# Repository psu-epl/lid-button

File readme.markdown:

LID Disco Button
----
Starting fresh? Go [here](https://github.com/psu-epl/lid-button/wiki)

Quick Links:

[Board Routing](https://github.com/psu-epl/lid-button/wiki/Board-Routing)

[Plating Thru Holes](https://github.com/psu-epl/lid-button/wiki/Plating-Thru-Holes)

[Testing the Board Part One](https://github.com/psu-epl/lid-button/wiki/Testing-the-board-Part-One)

[Solder Mask](https://github.com/psu-epl/lid-button/wiki/Applying-Solder-Mask)

[Solder Paste Stencil](https://github.com/psu-epl/lid-button/wiki/Solder-Paste-Stencil)

[Solder Paste](https://github.com/psu-epl/lid-button/wiki/Solder-Paste-Prep)

[Stuffing the board](https://github.com/psu-epl/lid-button/wiki/Stuffing-the-Board)

[Reflow Oven](https://github.com/psu-epl/lid-button/wiki/Reflow)

[Testing the Board Part Two](https://github.com/psu-epl/lid-button/wiki/Testing-The-Board-Part-Two)

[Programming the Microcontroller](https://github.com/psu-epl/lid-button/wiki/Coding-the-Board)

[Final Board Test](https://github.com/psu-epl/lid-button/wiki/Final-Board-Test)

[Enclosure Bottom](https://github.com/psu-epl/lid-button/wiki/Enclosure-Bottom)

[Enclosure Top](https://github.com/psu-epl/lid-button/wiki/Enclosure-Top)

[About this Project](https://github.com/psu-epl/lid-button/wiki/About-this-Project)

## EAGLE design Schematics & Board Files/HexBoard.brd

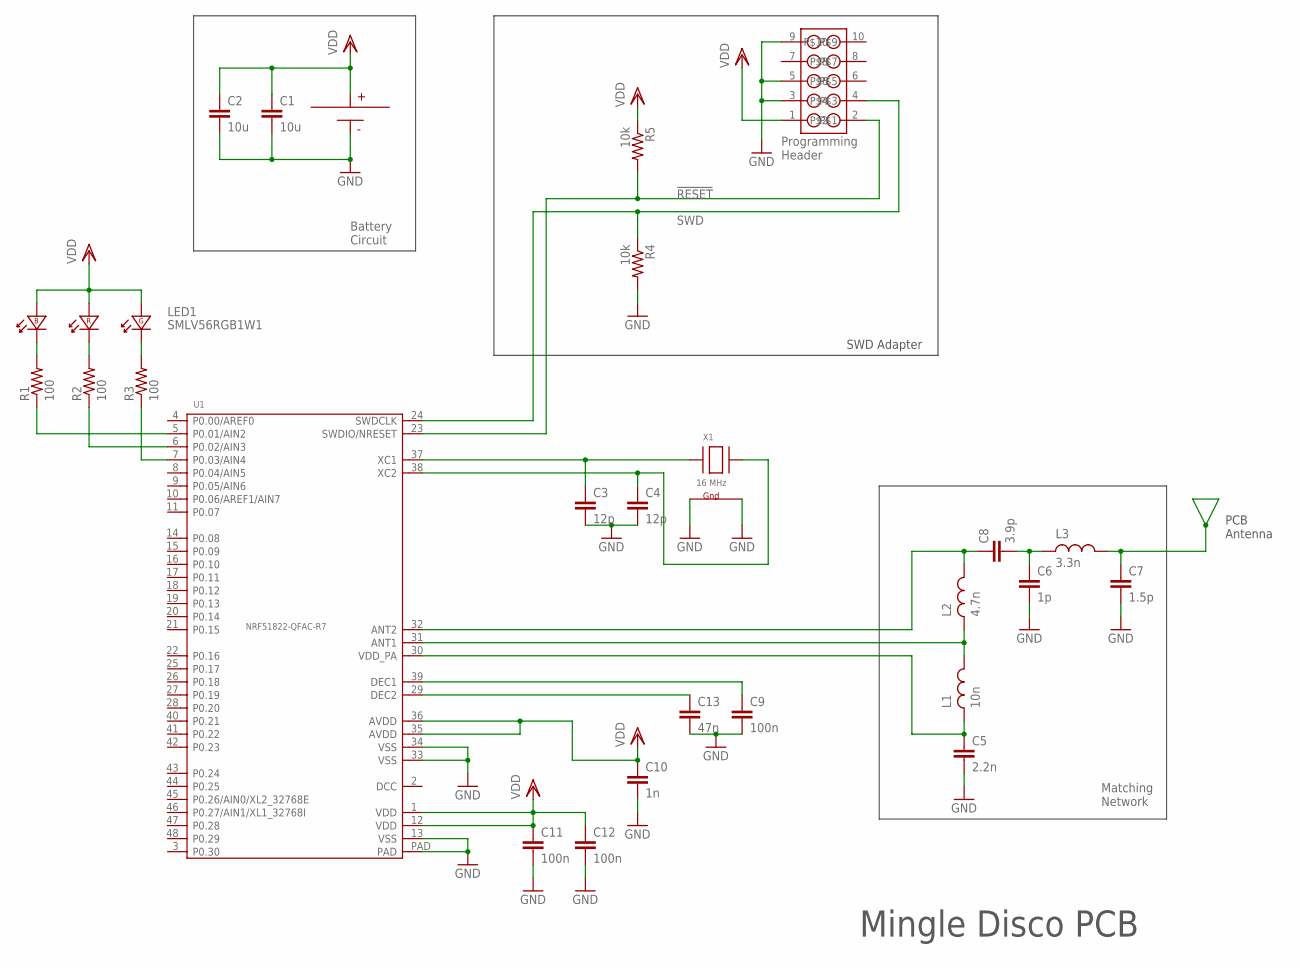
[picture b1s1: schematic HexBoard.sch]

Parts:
B1: CON-COINCEL-HOLDER-KEYSTONE-3012TR; 16MM-COINCELL-KEYSTONE
C1, C2: 10u; C0805
C3, C4: 12p; C0402
C5: 2.2n; C0402
C6: 1p; C0402
C7: 1.5p; C0402
C8: 3.9p; C0402
C9, C11, C12: 100n; C0402
C10: 1n; C0402
C13: 47n; C0402
L1: 10n; .0402-B-NOSILK
L2: 4.7n; .0402-B-NOSILK
L3: 3.3n; .0402-B-NOSILK
LED1: SMLV56RGB1W1; LED-3528
R1, R2, R3: 100; R0402
R4, R5: 10k; R0402
U1: NRF51822-QFAC-R7; QFN48-6X6MM
U$1: HEADER.05"PITCH
X1: 16 MHz; TXC_CRYSTAL

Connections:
!RESET: R5.2, U1.23 (SWDIO/NRESET), U$1.2
ANTENNA: C7.1, L3.2
GND: B1.NEG, C1.2, C2.2, C3.2, C4.2, C5.2, C6.2, C7.2, C9.2, C10.2, C11.2, C12.2, C13.2, R4.2, U1.13 (VSS), U1.33 (VSS), U1.34 (VSS), U1.PAD, U$1.3, U$1.5, U$1.9, X1.2 (G1), X1.4 (G2)
unnamed: LED1.6 (K), R1.2
unnamed: LED1.5 (K), R2.2
unnamed: LED1.4 (K), R3.2
unnamed: R1.1, U1.5 (P0.01/AIN2)
unnamed: R2.1, U1.6 (P0.02/AIN3)
unnamed: R3.1, U1.7 (P0.03/AIN4)
unnamed: C3.1, U1.37 (XC1), X1.1 (X1)
unnamed: C4.1, U1.38 (XC2), X1.3 (X2)
unnamed: L1.2, L2.1, U1.31 (ANT1)
unnamed: C9.1, U1.39 (DEC1)
unnamed: C6.1, C8.2, L3.1
unnamed: C8.1, L2.2, U1.32 (ANT2)
unnamed: C5.1, L1.1, U1.30 (VDD_PA)
unnamed: C13.1, U1.29 (DEC2)
SWD: R4.1, U1.24 (SWDCLK), U$1.4
VDD: B1.POS@1 (POS), B1.POS@2 (POS), C1.1, C2.1, C10.1, C11.1, C12.1, LED1.1 (A), LED1.2 (A), LED1.3 (A), R5.1, U1.1 (VDD), U1.12 (VDD), U1.35 (AVDD), U1.36 (AVDD), U$1.1

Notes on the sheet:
PCB Antenna
Battery Circuit
Programming Header
Matching Network
SWD Adapter
Mingle Disco PCB

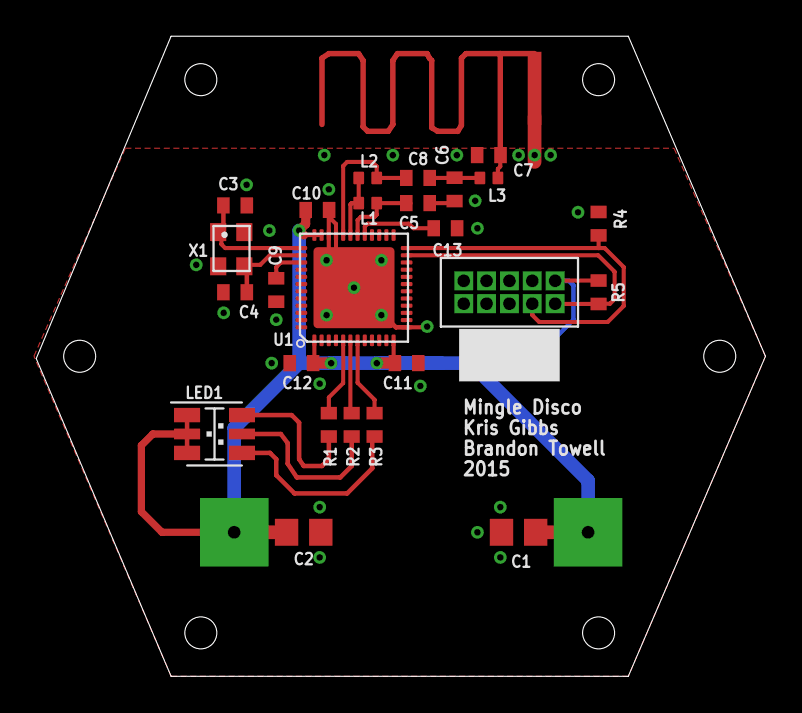
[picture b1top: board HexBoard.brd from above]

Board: 2 copper layers, 40.5 x 35.6 mm, 26 parts (1 on the bottom side), 19 nets.

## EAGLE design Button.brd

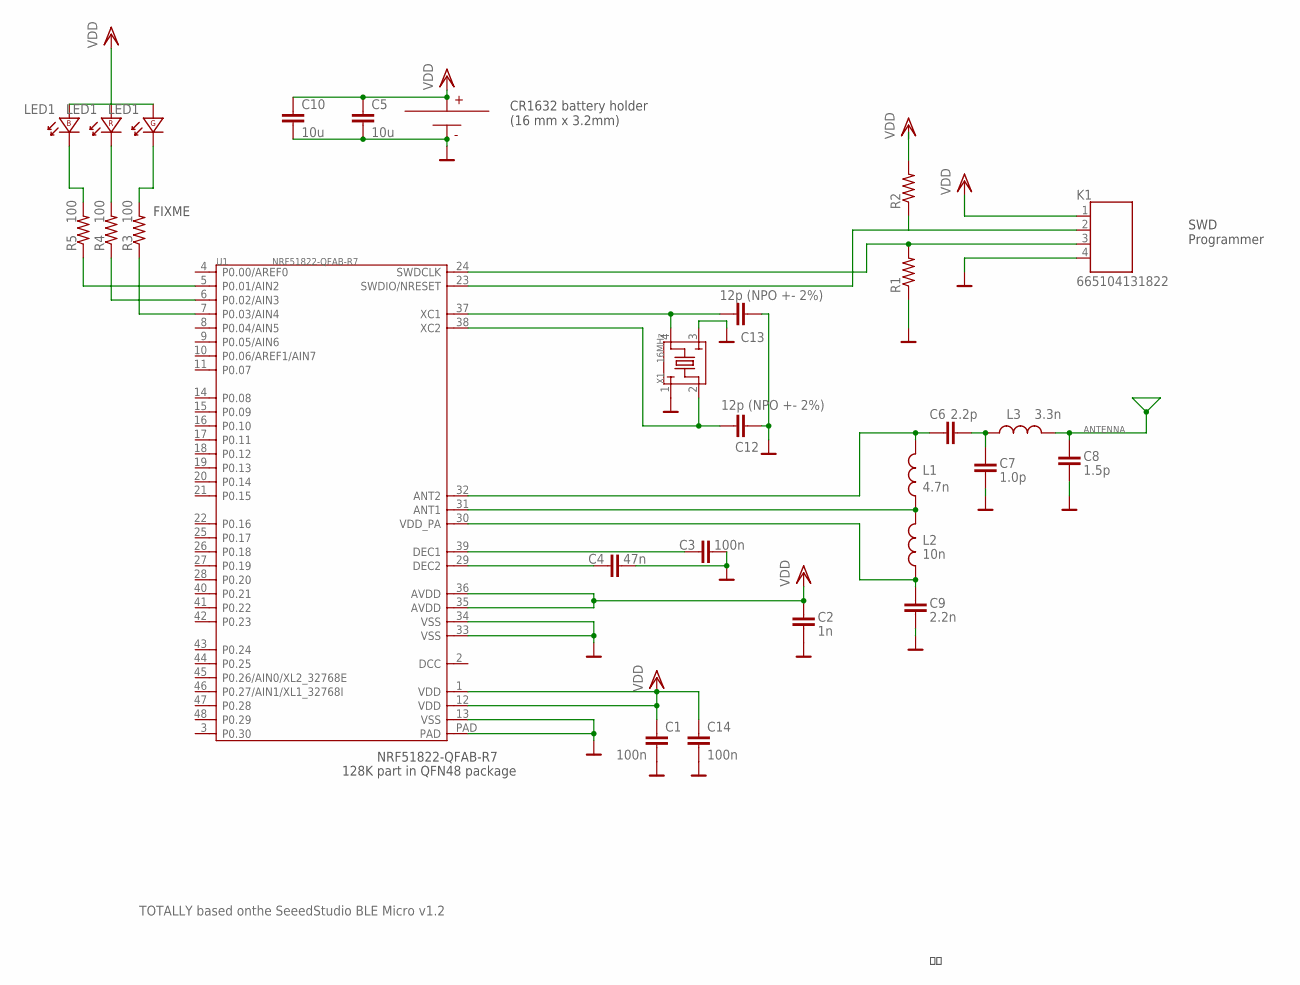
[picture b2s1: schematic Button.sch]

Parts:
B1: CON-COINCEL-HOLDER-KEYSTONE-3012TR; 16MM-COINCELL-KEYSTONE
C1, C3, C14: 100n; .0402-C-NOSILK
C2: 1n; .0402-C-NOSILK
C4: 47n; .0402-C-NOSILK
C5, C10: 10u; .0805-B-NOSILK
C6: 2.2p; .0402-C-NOSILK
C7: 1.0p; .0402-C-NOSILK
C8: 1.5p; .0402-C-NOSILK
C9: 2.2n; .0402-C-NOSILK
C12, C13: 12p (NPO +- 2%); .0402-C-NOSILK
K1: 665104131822
L1: 4.7n; .0402-C-NOSILK
L2: 10n; .0402-C-NOSILK
L3: 3.3n; .0402-C-NOSILK
LED1: LED-RGB-SEPARATE-3528; LED-3528
R1, R2: R-US_R0402; R0402
R3, R4, R5: 100; .0402-C-NOSILK
U1: NRF51822-QFAB-R7; QFN48-6X6MM
X1: 16MHz; 2520

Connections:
ANTENNA: C8.2, L3.2
GND: B1.NEG, C1.2, C2.2, C3.2, C4.2, C5.2, C7.1, C8.1, C9.2, C10.2, C12.2, C13.2, C14.2, K1.4, R1.1, U1.13 (VSS), U1.33 (VSS), U1.34 (VSS), U1.PAD, X1.1, X1.3
unnamed: R5.1, U1.5 (P0.01/AIN2)
unnamed: R4.1, U1.6 (P0.02/AIN3)
unnamed: R3.1, U1.7 (P0.03/AIN4)
unnamed: LED1.6 (K), R5.2
unnamed: LED1.5 (K), R4.2
unnamed: LED1.4 (K), R3.2
unnamed: K1.3, R1.2, U1.24 (SWDCLK)
unnamed: K1.2, R2.1, U1.23 (SWDIO/NRESET)
unnamed: C13.1, U1.37 (XC1), X1.4
unnamed: C12.1, U1.38 (XC2), X1.2
unnamed: C3.1, U1.39 (DEC1)
unnamed: C4.1, U1.29 (DEC2)
unnamed: C6.1, L1.2, U1.32 (ANT2)
unnamed: L1.1, L2.2, U1.31 (ANT1)
unnamed: C9.1, L2.1, U1.30 (VDD_PA)
unnamed: C6.2, C7.2, L3.1
VDD: B1.POS@1 (POS), B1.POS@2 (POS), C1.1, C2.1, C5.1, C10.1, C14.1, K1.1, LED1.1 (A), LED1.2 (A), LED1.3 (A), U1.1 (VDD), U1.12 (VDD), U1.35 (AVDD), U1.36 (AVDD)

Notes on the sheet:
TOTALLY based onthe SeeedStudio BLE Micro v1.2
CR1632 battery holder (16 mm x 3.2mm)
FIXME
SWD Programmer
NRF51822-QFAB-R7
128K part in QFN48 package

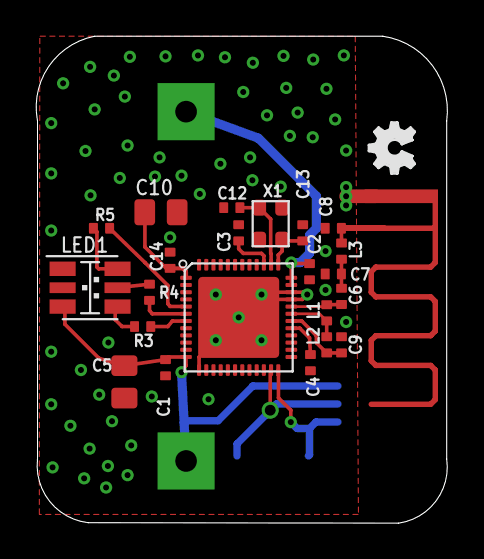
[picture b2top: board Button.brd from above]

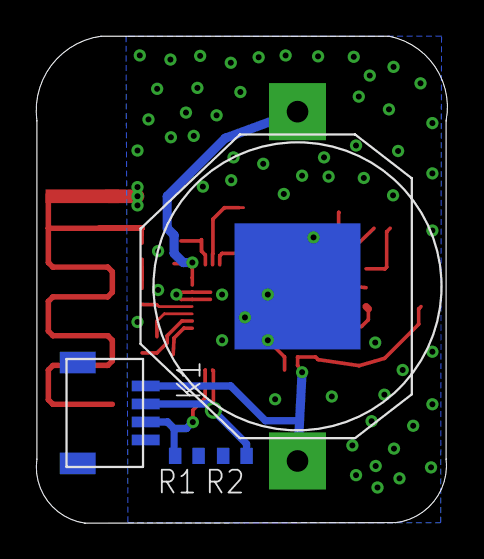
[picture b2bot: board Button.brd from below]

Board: 2 copper layers, 22.8 x 27.1 mm, 27 parts (4 on the bottom side), 19 nets.

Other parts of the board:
U$31: OSHW_FILLX100_NOTEXT

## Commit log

2015-01-29 creating lid-button repo!
2015-01-31 Clean up! This might acutally work (!). Removd 32KHz crystal, added 20 uF of bulk cap for spikes (might need more?). Biggest problem: antenna ok? Do we need the DC-DC converter to reduce the current 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
2015-01-31 First pass at BOM.
2015-02-13 Final board cleanup, including checking values and packages. Routed this one as a prototype on the A406. Also added BOM.
2015-07-10 Broke out libraries that we used to make the board.
2015-07-15 Added RGB footprint. Made a datasheet directory.
2015-09-04 Added some data sheets
2015-09-15 Adding Brd and such files for Button board update
2015-09-15 lasted version of brd and such
2015-09-16 gitignore file and makefile that will clean all the temp files
2015-10-06 new board design
    New board design Libraries included
2015-10-06 Code
    All Keil Project docs
2015-10-07 Main code file
    Adding just the code
2015-10-19 Folder reassignments
2015-10-19 New board design
2015-11-02 Board and schematic cleanup; see email to Kris today for notes.
2015-11-03 new project and main code
2015-11-03 Schematic clean up
2015-11-04 New code and maker guide documentation
2015-11-04 reverted HexBoard to previous version
2015-11-05 Latest code latest board and schematic updated maker guide
2015-11-16 OCD cleaned up of schematic -- nothing different, just prettyness. Cleaned up TNAMES layer a bit on board, checked DRC, moved a few vias... it's good to go. Sending off to OSH Parkgit add HexBoard.br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
2015-12-05 Merge remote-tracking branch 'origin/master'
    Conflicts:
    Schematics & Board Files/HexBoard.brd
2015-12-06 Adding photos
2015-12-10 Files from Kris.
2015-12-11 added pictures and case stl file
2015-12-11 added picture
2015-12-11 Edit BOM
2015-12-11 added pic
2015-12-11 Changed name of file
2015-12-11 Added enclosure files
2015-12-11 added more pictures
2015-12-11 Added new code and a picture
2015-12-11 added another photo
2015-12-11 added update library file and pictures

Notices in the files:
parts and their libraries:
Wurth_Elektronik_Electromechanic_Wire_to: Copyright: Würth Elektronik
